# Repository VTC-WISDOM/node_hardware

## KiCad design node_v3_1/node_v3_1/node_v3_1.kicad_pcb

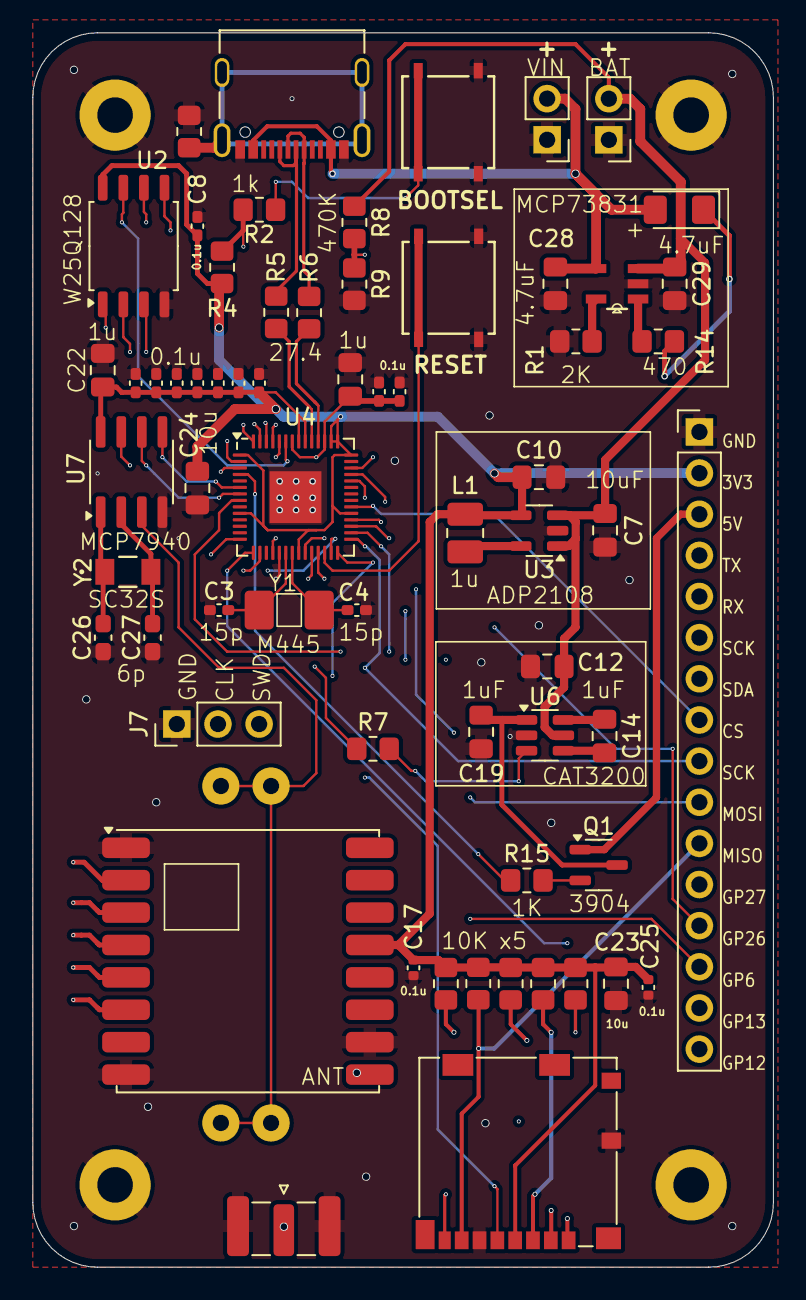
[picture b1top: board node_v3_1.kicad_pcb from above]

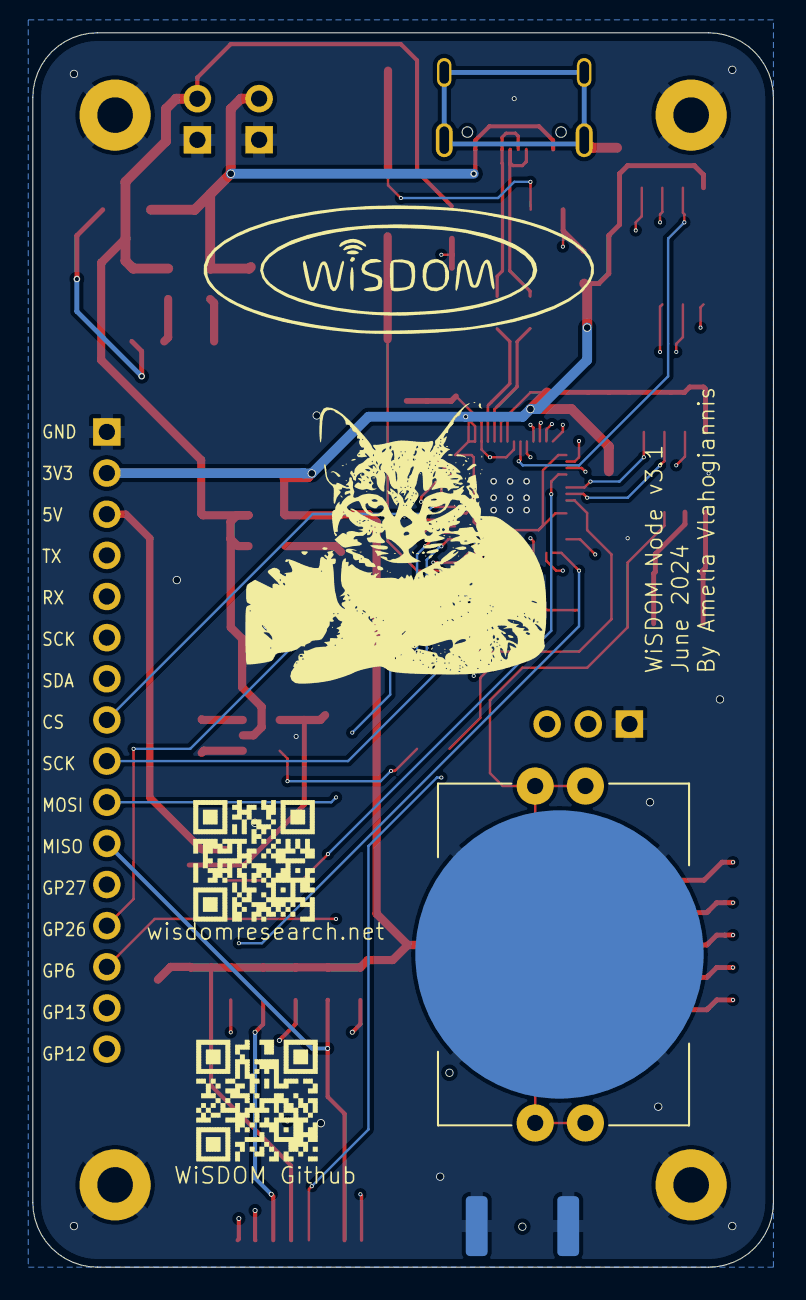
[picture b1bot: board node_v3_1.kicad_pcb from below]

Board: 4 copper layers, 45.7 x 76.2 mm, 71 parts (3 on the bottom side), 58 nets.

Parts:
BT1: Battery_Cell; BAT_BAT-HLD-001-THM
C3, C4: 15p; C_0402_1005Metric_Pad0.74x0.62mm_HandSolder
C5, C22: 1u; C_0805_2012Metric_Pad1.18x1.45mm_HandSolder
C6, C8, C9, C11, C13, C15, C16, C18, C20, C21: 100n; C_0402_1005Metric_Pad0.74x0.62mm_HandSolder
C7, C10: 10uF; C_0805_2012Metric_Pad1.18x1.45mm_HandSolder
C12, C14, C19: 1uF; C_0805_2012Metric_Pad1.18x1.45mm_HandSolder
C17: 0.1uF; C_0402_1005Metric
C23, C24: 10u; C_0805_2012Metric_Pad1.18x1.45mm_HandSolder
C25: .1u; C_0402_1005Metric
C26, C27: 6p; C_0603_1608Metric_Pad1.08x0.95mm_HandSolder
C28, C29: 4.7uF; C_0805_2012Metric_Pad1.18x1.45mm_HandSolder
D2: LED; LED_1206_3216Metric_Pad1.42x1.75mm_HandSolder
H1, H2, H3, H4: MountingHole_Pad; MountingHole_2.2mm_M2_Pad
J1: Conn_Coaxial; SMA_Samtec_SMA-J-P-H-ST-EM1_EdgeMount
J2: 12402012E212A; AMPHENOL_12402012E212A
J3: Micro_SD_Card; microSD_HC_Molex_104031-0811
J4: VIN; PinHeader_1x02_P2.54mm_Vertical
J5: BAT; PinHeader_1x02_P2.54mm_Vertical
J7: DBG; PinHeader_1x03_P2.54mm_Vertical
J8: Conn_01x16_Pin; PinHeader_1x16_P2.54mm_Vertical
L1: 1uH; L_1008_2520Metric_Pad1.43x2.20mm_HandSolder
LOGO: qrcode
LOGO#2: github_qr
Q1: 2N3904; SOT-23-3
R1: 2K; R_0805_2012Metric_Pad1.20x1.40mm_HandSolder
R2: 1k; R_0805_2012Metric_Pad1.20x1.40mm_HandSolder
R3, R7, R10, R11, R12, R16: 10K; R_0805_2012Metric_Pad1.20x1.40mm_HandSolder
R4: DNF; R_0805_2012Metric_Pad1.20x1.40mm_HandSolder
R5, R6: 27.4; R_0805_2012Metric_Pad1.20x1.40mm_HandSolder
R8, R9: 470K; R_0805_2012Metric_Pad1.20x1.40mm_HandSolder
R13: 0; R_0805_2012Metric_Pad1.20x1.40mm_HandSolder
R14: 470; R_0805_2012Metric_Pad1.20x1.40mm_HandSolder
R15: 1K; R_0805_2012Metric_Pad1.20x1.40mm_HandSolder
U1: RST; SMT_FS
U2: W25Q128JVS; SOIC-8_5.23x5.23mm_P1.27mm
U3: ADP2108AUJ-3.3; TSOT-23-5
U4: RP2040; QFN-56-1EP_7x7mm_P0.4mm_EP3.2x3.2mm
U5: RFM69HCW; HOPERF_RFM9XW_SMD
U6: CAT3200-5; SOT-23-6
U7: MCP7940N-xSN; SOIC-8_3.9x4.9mm_P1.27mm
U8: MCP73831T-2ACI_OT; SOT95P280X145-5N
U9: BOOTSEL; SMT_FS
Y1: 445C35A12M00000; XTAL-445
Y2: SC32S-7PF20PPM; XTAL_SC32S-7PF20PPM_EPS

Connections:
1V1: C5.1, C6.1, C9.1, U4.23 (DVDD), U4.45 (VREG_VOUT), U4.50 (DVDD)
3V3: C8.1, C10.1, C11.1, C13.1, C15.1, C16.1, C17.1, C18.1, C20.1, C21.1, C22.1, C23.1, C24.1, C25.1, J3.4 (VDD), J8.2, L1.2, R3.1, R4.1, R10.1, R11.1, R12.1, R16.1, U2.8 (VCC), U3.4 (FB), U4.1 (IOVDD), U4.10 (IOVDD), U4.22 (IOVDD), U4.33 (IOVDD), U4.42 (IOVDD), U4.43 (ADC_AVDD), U4.44 (VREG_IN), U4.48 (USB_VDD), U4.49 (IOVDD), U5.13 (3.3V), U7.8 (VCC)
5V: C19.1, Q1.3 (C), U6.1 (VOUT)
5V_CTRL: R7.2, U6.3 (~SHDN)
5V_OUT: J8.3, Q1.1 (E)
5V_SW: R15.1, U4.4 (GPIO2)
/ANT: J1.1 (In), U5.9 (ANT)
/USB_+: R5.2, U4.47 (USB_DP)
/USB_-: R6.2, U4.46 (USB_DM)
BAT: C7.1, C12.1, C29.1, J5.2, R8.1, U3.1 (Vin), U3.3 (EN), U6.5 (VIN), U8.3 (VBAT)
EXT_SW1: J8.16, U4.15 (GPIO12)
EXT_SW2: J8.15, U4.16 (GPIO13)
GND: BT1.N, C3.1, C4.1, C5.2, C6.2, C7.2, C8.2, C9.2, C10.2, C11.2, C12.2, C13.2, C15.2, C16.2, C17.2, C18.2, C19.2, C20.2, C21.2, C22.2, C23.2, C24.2, C25.2, C26.2, C27.2, C28.2, C29.2, H1.1, H2.1, H3.1, H4.1, J1.2 (Ext), J2.A1_B12 (GND), J2.B1_A12 (GND__1), J3.6 (VSS), J3.9 (SHIELD), J4.1, J5.1, J7.1, J8.1, R1.1, R9.2, R13.2, U1.1, U1.2, U2.4 (GND), U3.2 (GND), U4.19 (TESTEN), U4.57 (GND), U5.1 (GND), U5.8 (GND), U5.10 (GND), U6.2 (GND), U7.4 (VSS), U8.2 (VSS), U9.1, U9.2
GP6: J8.14, U4.8 (GPIO6)
GP26: J8.13, U4.38 (GPIO26_ADC0)
GP27: J8.12, U4.39 (GPIO27_ADC1)
I2C_SCK: J8.6, U4.7 (GPIO5), U7.6 (SCL)
I2C_SDA: J8.7, U4.6 (GPIO4), U7.5 (SDA)
MISO: J3.7 (DAT0), J8.11, R11.2, U4.27 (GPIO16), U5.2 (MISO)
MOSI: J3.3 (CMD), J8.10, R3.2, U4.30 (GPIO19), U5.3 (MOSI)
unnamed: BT1.P1, BT1.P2, BT1.P3, BT1.P4, U7.3 (VBAT)
unnamed: D2.1 (K), R14.1
unnamed: J2.SH1 (SHIELD), J2.SH2 (SHIELD__1), J2.SH3 (SHIELD__2), J2.SH4 (SHIELD__3), R13.1
unnamed: J3.8 (DAT1), R16.2
unnamed: J3.1 (DAT2), R10.2
unnamed: Q1.2 (B), R15.2
unnamed: R2.1, U9.3, U9.4
unnamed: L1.1, U3.5 (SW)
unnamed: R7.1, U4.14 (GPIO11)
unnamed: R8.2, R9.1, U4.40 (GPIO28_ADC2)
unnamed: U1.3, U1.4, U4.26 (RUN)
unnamed: C3.2, U4.20 (XIN), Y1.2
unnamed: C4.2, U4.21 (XOUT), Y1.1
unnamed: C14.2, U6.4 (CNEG)
unnamed: C14.1, U6.6 (CPOS)
unnamed: C26.1, U7.1 (X1), Y2.1
unnamed: C27.1, U7.2 (X2), Y2.2
unnamed: R1.2, U8.5 (PROG)
unnamed: R14.2, U8.1 (STAT)
QSPI_CLK: U2.6 (CLK), U4.52 (QSPI_SCLK)
QSPI_CS: R2.2, R4.2, U2.1 (~CS), U4.56 (QSPI_SS)
QSPI_SD0: U2.5 (DI(IO0)), U4.53 (QSPI_SD0)
QSPI_SD1: U2.2 (DO(IO1)), U4.55 (QSPI_SD1)
QSPI_SD2: U2.3 (IO2), U4.54 (QSPI_SD2)
QSPI_SD3: U2.7 (IO3), U4.51 (QSPI_SD3)
RFM_CS: U4.28 (GPIO17), U5.5 (NSS)
RFM_RST: U4.31 (GPIO20), U5.6 (RESET)
RTC_MFP: U4.18 (GPIO15), U7.7 (MFP)
SD_CS: J3.2 (DAT3/CD), R12.2, U4.32 (GPIO21)
SPI_CS: J8.8, U4.34 (GPIO22)
SPI_SCK: J3.5 (CLK), J8.9, U4.29 (GPIO18), U5.4 (SCK)
SWD: J7.3, U4.25 (SWD)
SWDCLK: J7.2, U4.24 (SWCLK)
UART_RX: J8.5, U4.3 (GPIO1)
UART_TX: J8.4, U4.2 (GPIO0)
USB+: J2.A6 (D+_A), J2.B6 (D+_B), R5.1
USB-: J2.A7 (D-_A), J2.B7 (D-_B), R6.1
VIN: C28.1, D2.2 (A), J2.A4_B9 (VBUS), J2.B4_A9 (VBUS__1), J4.2, U8.4 (VDD)

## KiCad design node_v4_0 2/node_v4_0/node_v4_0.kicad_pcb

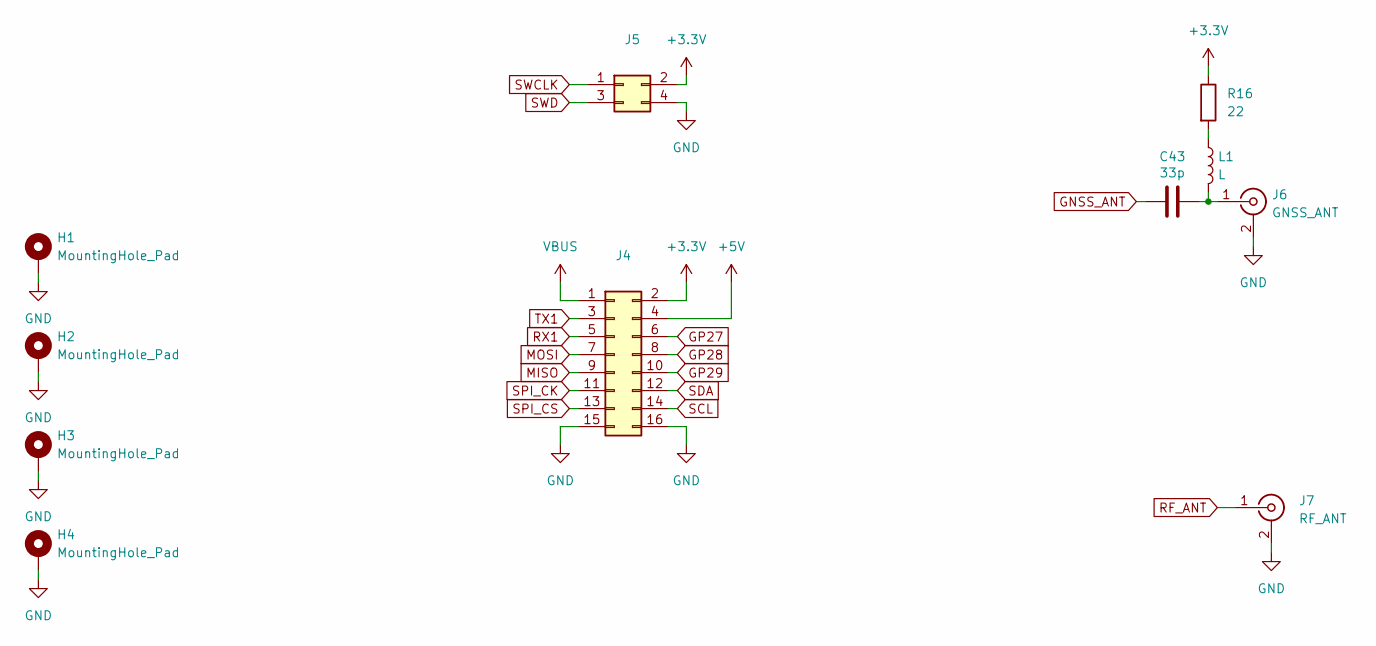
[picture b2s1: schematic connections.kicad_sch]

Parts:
C43: 33p; C_0402_1005Metric_Pad0.74x0.62mm_HandSolder
H1, H2, H3, H4: MountingHole_Pad; MountingHole_2.2mm_M2_Pad_TopBottom
J4: Conn_02x08_Odd_Even; PinHeader_2x08_P2.54mm_Vertical
J5: Conn_02x02_Odd_Even; PinHeader_2x02_P2.54mm_Vertical
J6: GNSS_ANT; CONN_CONMHF1-SMD_LNX
J7: RF_ANT; CONN_CONMHF1-SMD_LNX
L1: L; L_0402_1005Metric_Pad0.77x0.64mm_HandSolder
R16: 22; R_0805_2012Metric_Pad1.20x1.40mm_HandSolder

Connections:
+5V: J4.4; also elsewhere on the board
GND: H1.1, H2.1, H3.1, H4.1, J4.15, J4.16, J5.4, J6.2 (Ext), J7.2 (Ext); also elsewhere on the board
GNSS_ANT: C43.1; also elsewhere on the board
GP27: J4.6; also elsewhere on the board
GP28: J4.8; also elsewhere on the board
GP29: J4.10; also elsewhere on the board
MISO: J4.9; also elsewhere on the board
MOSI: J4.7; also elsewhere on the board
unnamed: C43.2, J6.1 (In), L1.2
unnamed: L1.1, R16.2
RF_ANT: J7.1 (In); also elsewhere on the board
RX1: J4.5; also elsewhere on the board
SCL: J4.14; also elsewhere on the board
SDA: J4.12; also elsewhere on the board
SPI_CK: J4.11; also elsewhere on the board
SPI_CS: J4.13; also elsewhere on the board
SWCLK: J5.1; also elsewhere on the board
SWD: J5.3; also elsewhere on the board
TX1: J4.3; also elsewhere on the board
VBUS: J4.1; also elsewhere on the board

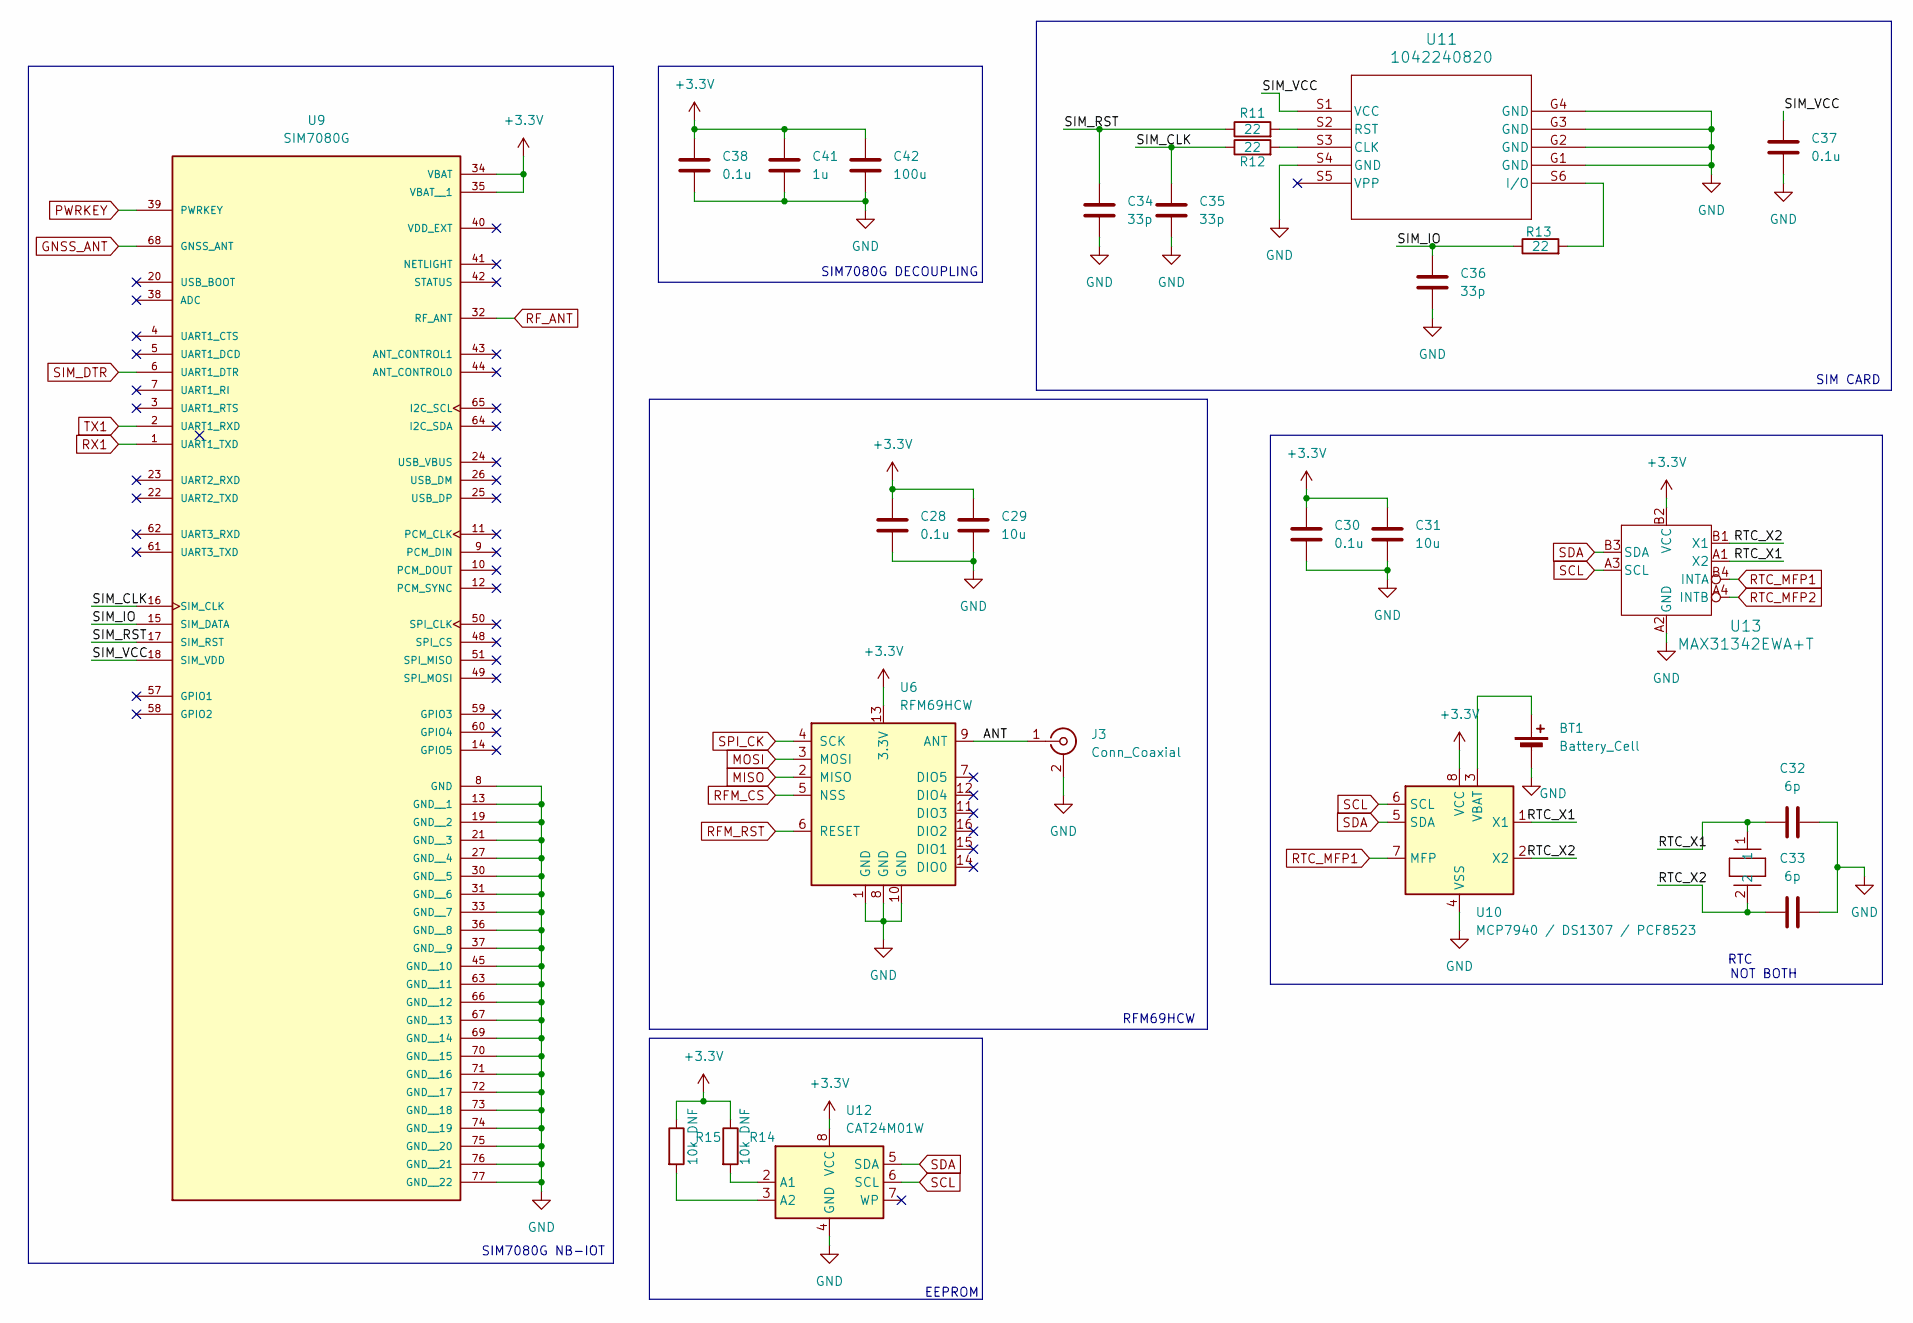
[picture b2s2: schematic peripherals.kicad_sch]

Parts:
BT1: Battery_Cell; BAT_BAT-HLD-001-THM
C28, C30, C37, C38: 0.1u; C_0402_1005Metric_Pad0.74x0.62mm_HandSolder
C29, C31: 10u; C_0805_2012Metric_Pad1.18x1.45mm_HandSolder
C32, C33: 6p; C_0201_0603Metric_Pad0.64x0.40mm_HandSolder
C34, C35, C36: 33p; C_0402_1005Metric_Pad0.74x0.62mm_HandSolder
C41: 1u; C_0805_2012Metric_Pad1.18x1.45mm_HandSolder
C42: 100u; C_0805_2012Metric_Pad1.18x1.45mm_HandSolder
J3: Conn_Coaxial; SMA_Samtec_SMA-J-P-H-ST-EM1_EdgeMount
R11, R12, R13: 22; C_0805_2012Metric_Pad1.18x1.45mm_HandSolder
R14, R15: 10k DNF; R_0402_1005Metric_Pad0.72x0.64mm_HandSolder
U6: RFM69HCW; HOPERF_RFM9XW_SMD
U9: SIM7080G; XCVR_SIM7080G; PARTREV 1.04
U10: MCP7940 / DS1307 / PCF8523; SOIC-8_3.9x4.9mm_P1.27mm
U11: 1042240820; 1042240820_MOL
U12: CAT24M01W; SOIC-8_3.9x4.9mm_P1.27mm
U13: MAX31342EWA+T; 21-100291_W80D&plus_1_MXM
XTAL1: SC32S-7PF20PPM; XTAL_SC32S-7PF20PPM_EPS

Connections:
/PERIPHERALS/ANT: J3.1 (In), U6.9 (ANT)
/PERIPHERALS/RTC_X1: C32.1, U10.1 (X1), U13.A1 (X2), XTAL1.1
/PERIPHERALS/RTC_X2: C33.1, U10.2 (X2), U13.B1 (X1), XTAL1.2
/PERIPHERALS/SIM_CLK: C35.1, R12.1, U9.16 (SIM_CLK)
/PERIPHERALS/SIM_IO: C36.1, R13.1, U9.15 (SIM_DATA)
/PERIPHERALS/SIM_RST: C34.1, R11.1, U9.17 (SIM_RST)
/PERIPHERALS/SIM_VCC: C37.1, U9.18 (SIM_VDD), U11.S1 (VCC)
GND: BT1.2 (-), C28.2, C29.2, C30.2, C31.2, C32.2, C33.2, C34.2, C35.2, C36.2, C37.2, C38.2, C41.2, C42.2, J3.2 (Ext), U6.1 (GND), U6.8 (GND), U6.10 (GND), U9.8 (GND), U9.13 (GND__1), U9.19 (GND__2), U9.21 (GND__3), U9.27 (GND__4), U9.30 (GND__5), U9.31 (GND__6), U9.33 (GND__7), U9.36 (GND__8), U9.37 (GND__9), U9.45 (GND__10), U9.63 (GND__11), U9.66 (GND__12), U9.67 (GND__13), U9.69 (GND__14), U9.70 (GND__15), U9.71 (GND__16), U9.72 (GND__17), U9.73 (GND__18), U9.74 (GND__19), U9.75 (GND__20), U9.76 (GND__21), U9.77 (GND__22), U10.4 (VSS), U11.G1 (GND), U11.G2 (GND), U11.G3 (GND), U11.G4 (GND), U11.S4 (GND), U12.4 (GND), U13.A2 (GND); also elsewhere on the board
GNSS_ANT: U9.68 (GNSS_ANT); also elsewhere on the board
MISO: U6.2 (MISO); also elsewhere on the board
MOSI: U6.3 (MOSI); also elsewhere on the board
unnamed: R12.2, U11.S3 (CLK)
unnamed: R13.2, U11.S6 (I/O)
unnamed: R11.2, U11.S2 (RST)
unnamed: R14.2, U12.2 (A1)
unnamed: R15.2, U12.3 (A2)
PWRKEY: U9.39 (PWRKEY)
RFM_CS: U6.5 (NSS); also elsewhere on the board
RFM_RST: U6.6 (RESET); also elsewhere on the board
RF_ANT: U9.32 (RF_ANT); also elsewhere on the board
RTC_MFP1: U10.7 (MFP), U13.B4 (INTA); also elsewhere on the board
RTC_MFP2: U13.A4 (INTB); also elsewhere on the board
RX1: U9.1 (UART1_TXD); also elsewhere on the board
SCL: U10.6 (SCL), U12.6 (SCL), U13.A3 (SCL); also elsewhere on the board
SDA: U10.5 (SDA), U12.5 (SDA), U13.B3 (SDA); also elsewhere on the board
SIM_DTR: U9.6 (UART1_DTR); also elsewhere on the board
SPI_CK: U6.4 (SCK); also elsewhere on the board
TX1: U9.2 (UART1_RXD); also elsewhere on the board

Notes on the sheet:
RFM69HCW
EEPROM
SIM7080G DECOUPLING
RTC
SIM CARD
SIM7080G NB-IOT
NOT BOTH

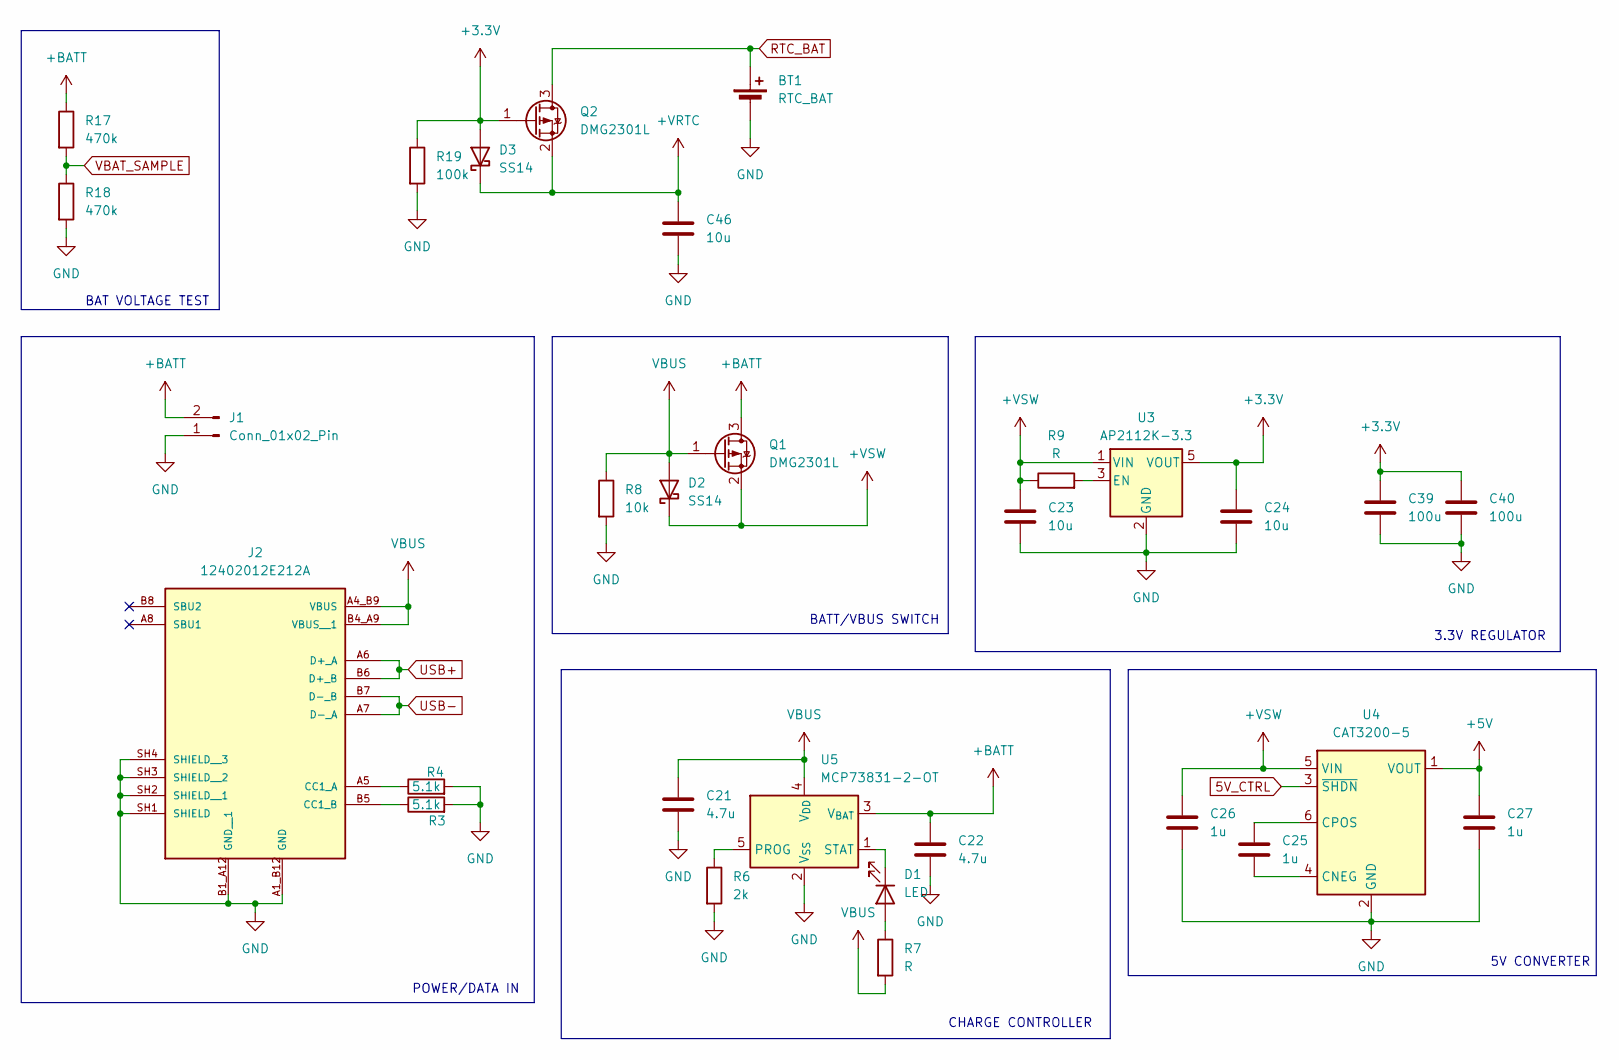
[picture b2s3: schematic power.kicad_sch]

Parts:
BT1: RTC_BAT; BAT_BAT-HLD-001-THM
C21, C22: 4.7u; C_0805_2012Metric_Pad1.18x1.45mm_HandSolder
C23, C24, C46: 10u; C_0805_2012Metric_Pad1.18x1.45mm_HandSolder
C25, C26, C27: 1u; C_0805_2012Metric_Pad1.18x1.45mm_HandSolder
C39, C40: 100u; C_0805_2012Metric_Pad1.18x1.45mm_HandSolder
D1: LED; LED_1206_3216Metric_Pad1.42x1.75mm_HandSolder
D2, D3: SS14; D_SMA
J1: Conn_01x02_Pin; JST_PH_S2B-PH-K_1x02_P2.00mm_Horizontal
J2: 12402012E212A; AMPHENOL_12402012E212A; PARTREV 4
Q1, Q2: DMG2301L; SOT-23
R3, R4: 5.1k; R_0805_2012Metric_Pad1.20x1.40mm_HandSolder
R6: 2k; R_0805_2012Metric_Pad1.20x1.40mm_HandSolder
R7, R9: R; R_0805_2012Metric_Pad1.20x1.40mm_HandSolder
R8: 10k; R_0805_2012Metric_Pad1.20x1.40mm_HandSolder
R17, R18: 470k; R_0805_2012Metric_Pad1.20x1.40mm_HandSolder
R19: 100k; R_0805_2012Metric_Pad1.20x1.40mm_HandSolder
U3: AP2112K-3.3; SOT-23-5
U4: CAT3200-5; SOT-23-6
U5: MCP73831-2-OT; SOT-23-5

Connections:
5V_CTRL: U4.3 (~SHDN)
+5V: C27.1, U4.1 (VOUT); also elsewhere on the board
+BATT: C22.1, J1.2, Q1.3 (D), R17.1, U5.3 (V_{BAT})
+VSW: C23.1, C26.1, D2.1 (K), Q1.2 (S), R9.1, U3.1 (VIN), U4.5 (VIN)
GND: BT1.2 (-), C21.2, C22.2, C23.2, C24.2, C26.2, C27.2, C39.2, C40.2, C46.2, J1.1, J2.A1_B12 (GND), J2.B1_A12 (GND__1), J2.SH1 (SHIELD), J2.SH2 (SHIELD__1), J2.SH3 (SHIELD__2), J2.SH4 (SHIELD__3), R3.2, R4.2, R6.2, R8.2, R18.2, R19.2, U3.2 (GND), U4.2 (GND), U5.2 (V_{SS}); also elsewhere on the board
unnamed: D1.2 (A), R7.1
unnamed: D1.1 (K), U5.1 (STAT)
unnamed: J2.A5 (CC1_A), R4.1
unnamed: J2.B5 (CC1_B), R3.1
unnamed: R9.2, U3.3 (EN)
unnamed: C25.2, U4.4 (CNEG)
unnamed: C25.1, U4.6 (CPOS)
unnamed: R6.1, U5.5 (PROG)
USB+: J2.A6 (D+_A), J2.B6 (D+_B); also elsewhere on the board
USB-: J2.A7 (D-_A), J2.B7 (D-_B); also elsewhere on the board
VBAT_SAMPLE: R17.2, R18.1; also elsewhere on the board
VBUS: C21.1, D2.2 (A), J2.A4_B9 (VBUS), J2.B4_A9 (VBUS__1), Q1.1 (G), R7.2, R8.1, U5.4 (V_{DD}); also elsewhere on the board

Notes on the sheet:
POWER/DATA IN
BATT/VBUS SWITCH
5V CONVERTER
BAT VOLTAGE TEST
3.3V REGULATOR
CHARGE CONTROLLER

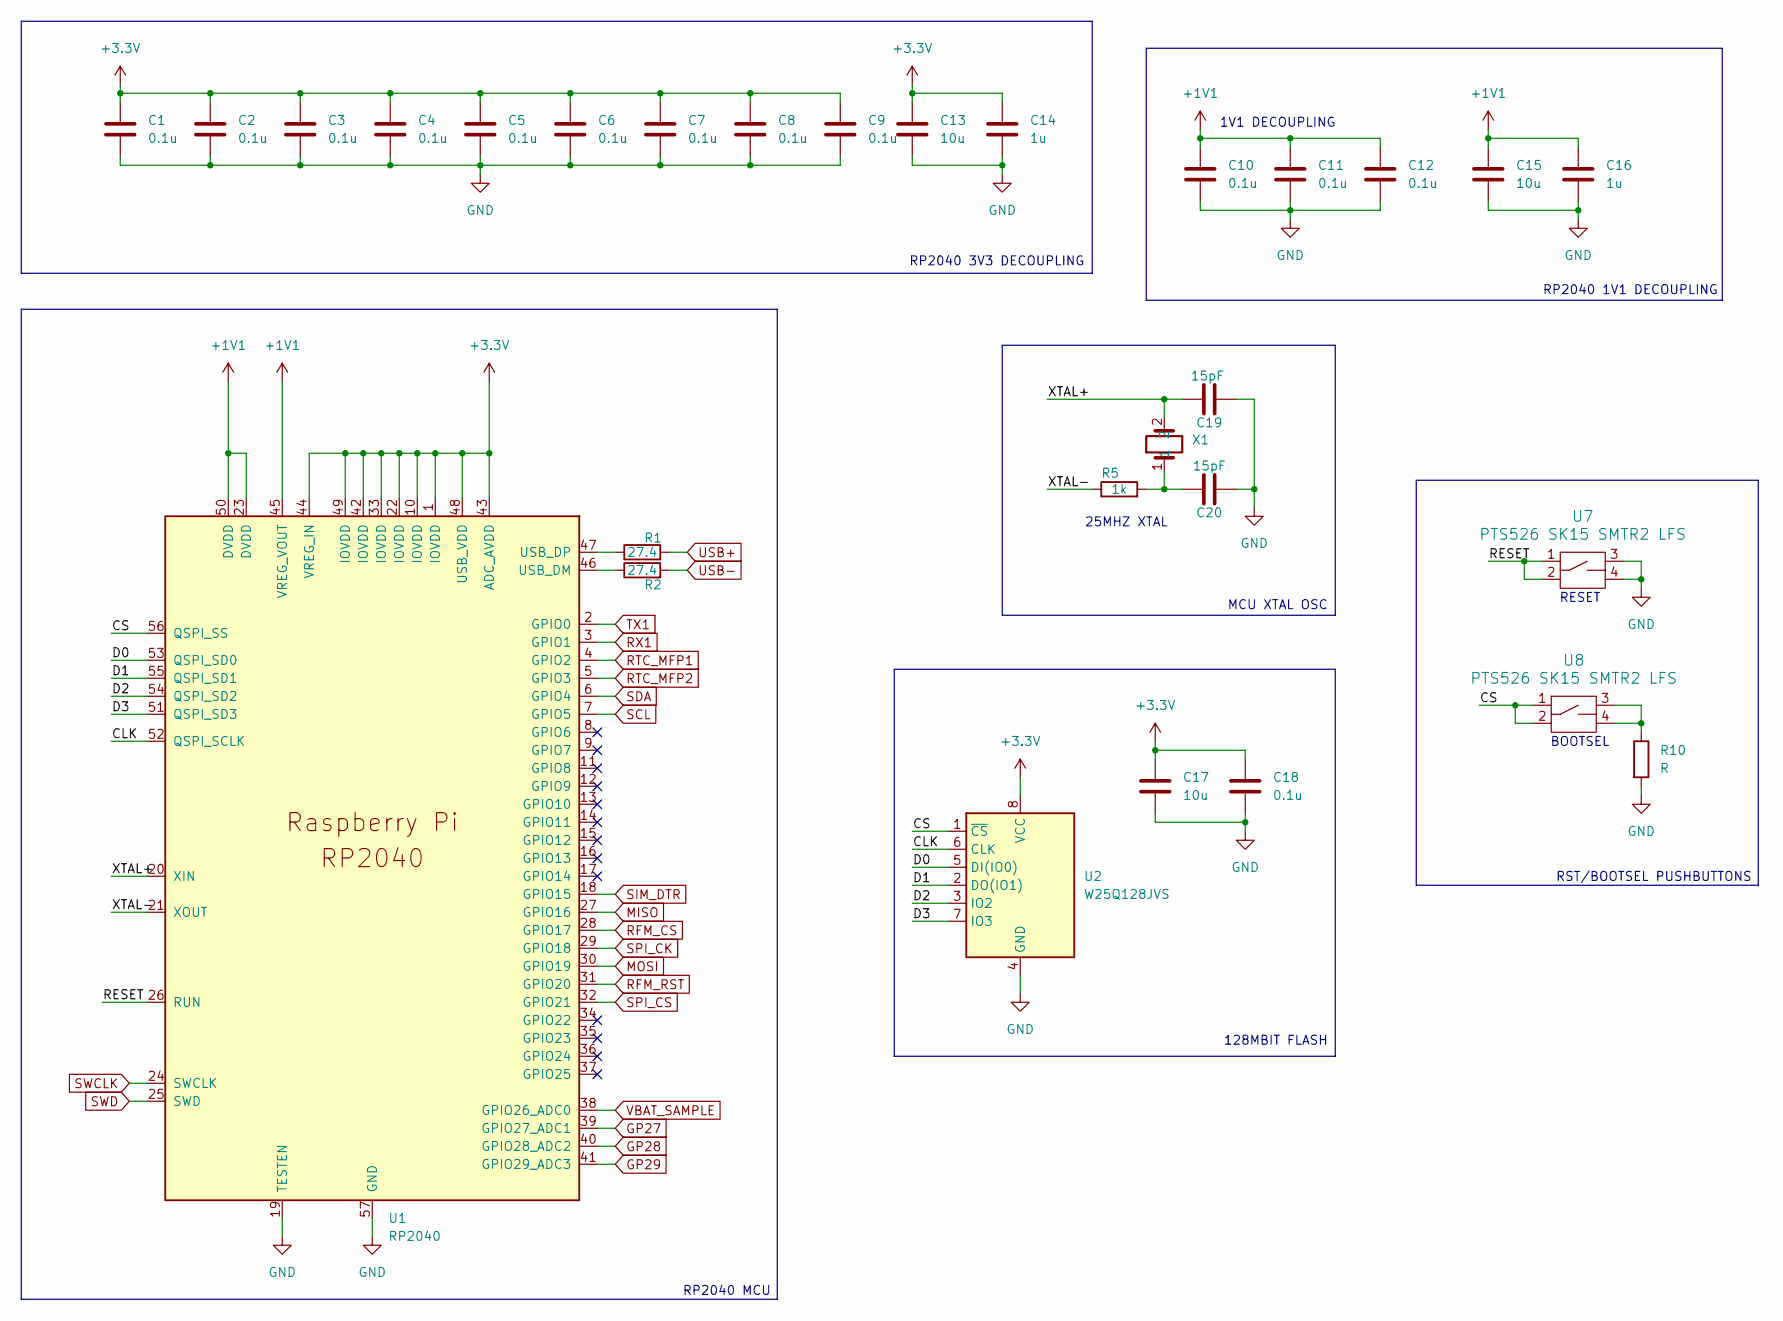
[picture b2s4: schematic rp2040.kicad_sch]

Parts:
C1, C2, C3, C4, C5, C6, C7, C8, C9, C10, C11, C12, C18: 0.1u; C_0402_1005Metric_Pad0.74x0.62mm_HandSolder
C13, C15, C17: 10u; C_0805_2012Metric_Pad1.18x1.45mm_HandSolder
C14, C16: 1u; C_0805_2012Metric_Pad1.18x1.45mm_HandSolder
C19, C20: 15pF; C_0402_1005Metric_Pad0.74x0.62mm_HandSolder
R1, R2: 27.4; R_0603_1608Metric_Pad0.98x0.95mm_HandSolder
R5: 1k; R_0805_2012Metric_Pad1.20x1.40mm_HandSolder
R10: R; R_0805_2012Metric_Pad1.20x1.40mm_HandSolder
U1: RP2040; RP2040-QFN-56
U2: W25Q128JVS; SOIC-8_5.23x5.23mm_P1.27mm
U7, U8: PTS526 SK15 SMTR2 LFS; PTS526
X1: XTAL-445

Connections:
+1V1: C10.1, C11.1, C12.1, C15.1, C16.1, U1.23 (DVDD), U1.45 (VREG_VOUT), U1.50 (DVDD)
/MCU/CLK: U1.52 (QSPI_SCLK), U2.6 (CLK)
/MCU/CS: U1.56 (QSPI_SS), U2.1 (~CS), U8.1, U8.2
/MCU/D0: U1.53 (QSPI_SD0), U2.5 (DI(IO0))
/MCU/D1: U1.55 (QSPI_SD1), U2.2 (DO(IO1))
/MCU/D2: U1.54 (QSPI_SD2), U2.3 (IO2)
/MCU/D3: U1.51 (QSPI_SD3), U2.7 (IO3)
/MCU/RESET: U1.26 (RUN), U7.1, U7.2
/MCU/XTAL+: C19.1, U1.20 (XIN), X1.2
/MCU/XTAL-: R5.1, U1.21 (XOUT)
GND: C1.2, C2.2, C3.2, C4.2, C5.2, C6.2, C7.2, C8.2, C9.2, C10.2, C11.2, C12.2, C13.2, C14.2, C15.2, C16.2, C17.2, C18.2, C19.2, C20.2, R10.2, U1.19 (TESTEN), U1.57 (GND), U2.4 (GND), U7.3, U7.4; also elsewhere on the board
GP27: U1.39 (GPIO27_ADC1); also elsewhere on the board
GP28: U1.40 (GPIO28_ADC2); also elsewhere on the board
GP29: U1.41 (GPIO29_ADC3); also elsewhere on the board
MISO: U1.27 (GPIO16); also elsewhere on the board
MOSI: U1.30 (GPIO19); also elsewhere on the board
unnamed: C20.1, R5.2, X1.1
unnamed: R10.1, U8.3, U8.4
unnamed: R2.1, U1.46 (USB_DM)
unnamed: R1.1, U1.47 (USB_DP)
RFM_CS: U1.28 (GPIO17); also elsewhere on the board
RFM_RST: U1.31 (GPIO20); also elsewhere on the board
RTC_MFP1: U1.4 (GPIO2); also elsewhere on the board
RTC_MFP2: U1.5 (GPIO3); also elsewhere on the board
RX1: U1.3 (GPIO1); also elsewhere on the board
SCL: U1.7 (GPIO5); also elsewhere on the board
SDA: U1.6 (GPIO4); also elsewhere on the board
SIM_DTR: U1.18 (GPIO15); also elsewhere on the board
SPI_CK: U1.29 (GPIO18); also elsewhere on the board
SPI_CS: U1.32 (GPIO21); also elsewhere on the board
SWCLK: U1.24 (SWCLK); also elsewhere on the board
SWD: U1.25 (SWD); also elsewhere on the board
TX1: U1.2 (GPIO0); also elsewhere on the board
USB+: R1.2; also elsewhere on the board
USB-: R2.2; also elsewhere on the board
VBAT_SAMPLE: U1.38 (GPIO26_ADC0); also elsewhere on the board

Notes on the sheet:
RST/BOOTSEL PUSHBUTTONS
RP2040 3V3 DECOUPLING
RP2040 MCU
RESET
RP2040 1V1 DECOUPLING
BOOTSEL
MCU XTAL OSC
1V1 DECOUPLING
25MHZ XTAL
128MBIT FLASH

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
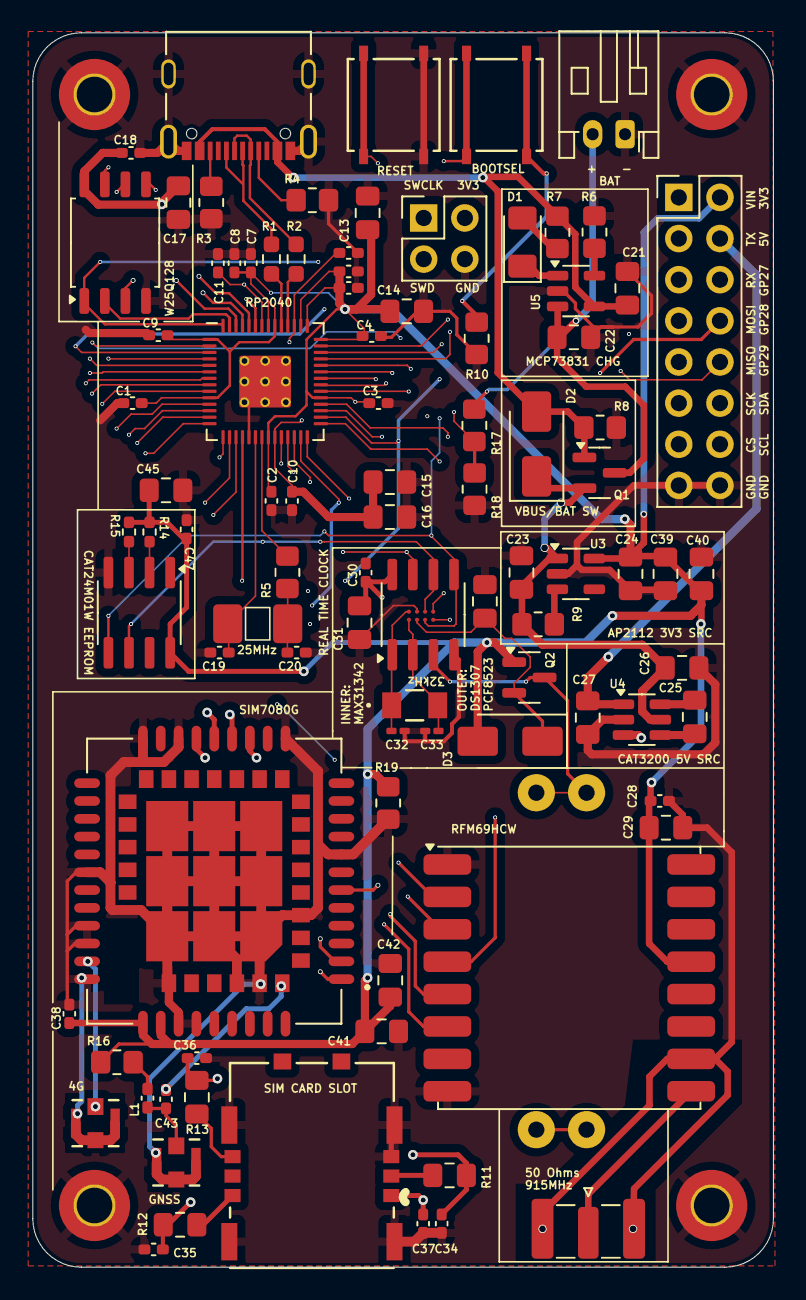
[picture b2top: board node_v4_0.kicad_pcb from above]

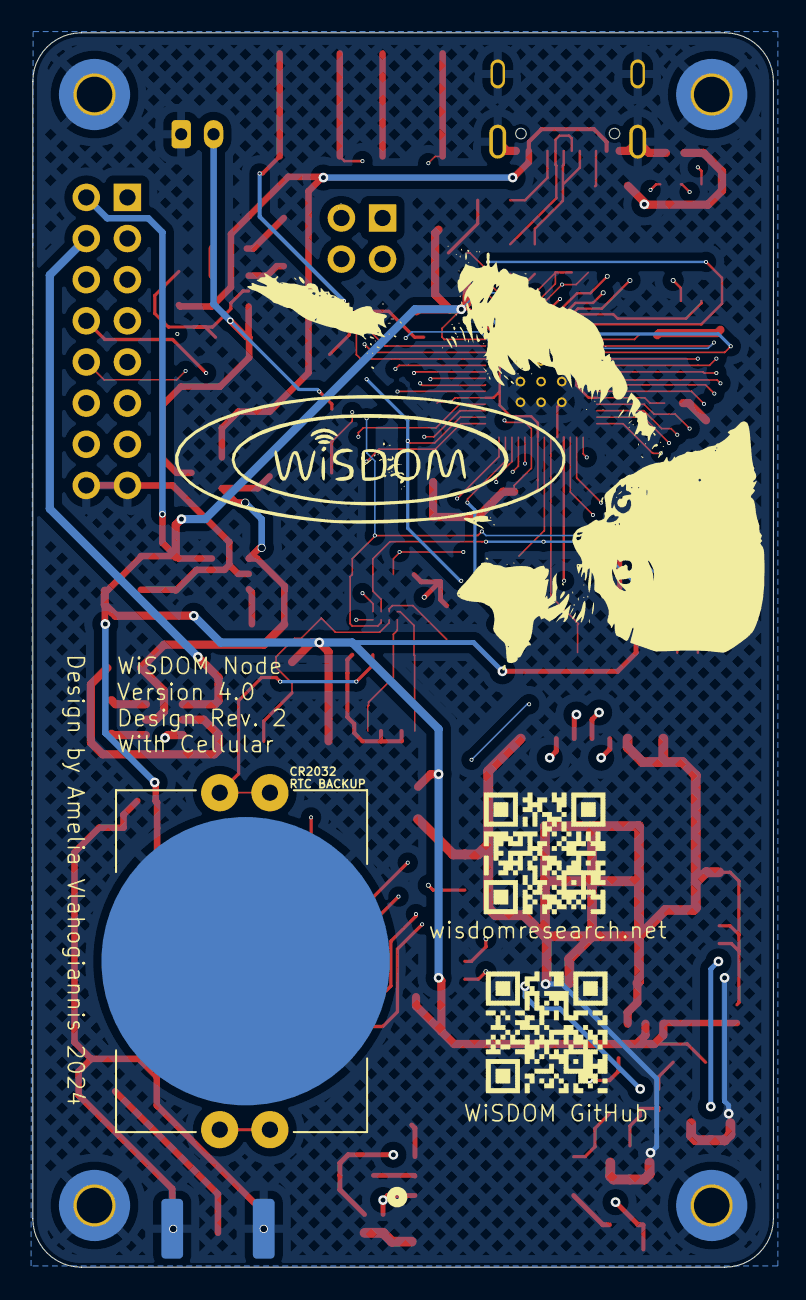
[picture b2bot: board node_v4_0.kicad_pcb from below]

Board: 4 copper layers, 45.7 x 76.2 mm, 100 parts (3 on the bottom side), 67 nets.

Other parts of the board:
C44: 0.1u; C_0402_1005Metric_Pad0.74x0.62mm_HandSolder
C45: 10u; C_0805_2012Metric_Pad1.18x1.45mm_HandSolder
LOGO: qrcode
LOGO#2: github_qr

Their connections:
GND: C44.2, C45.2; also elsewhere on the board
